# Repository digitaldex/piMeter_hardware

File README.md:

# piMeter - a SmartMeter for Raspberry Pi

Repo got cleaned up. You can find the new Software Version in my [piMeter_grafana](https://github.com/digitaldex/piMeter_grafana) Repo.

This one here is now only for the Hardware Part of this Project.

## Board

## Case

## Schematics
[piMeter Schematics](https://github.com/digitaldex/piMeter_hardware/blob/master/eagle/Schematics.pdf)

## Ressources

[ADE9000 Datasheet](http://www.analog.com/media/en/technical-documentation/data-sheets/ADE9000.pdf)

[bcm2835 Library](http://www.airspayce.com/mikem/bcm2835/)

[InfluxDB Library](https://github.com/orca-zhang/influxdb-cpp)

[www.digitaldex.de](http://www.digitaldex.de)

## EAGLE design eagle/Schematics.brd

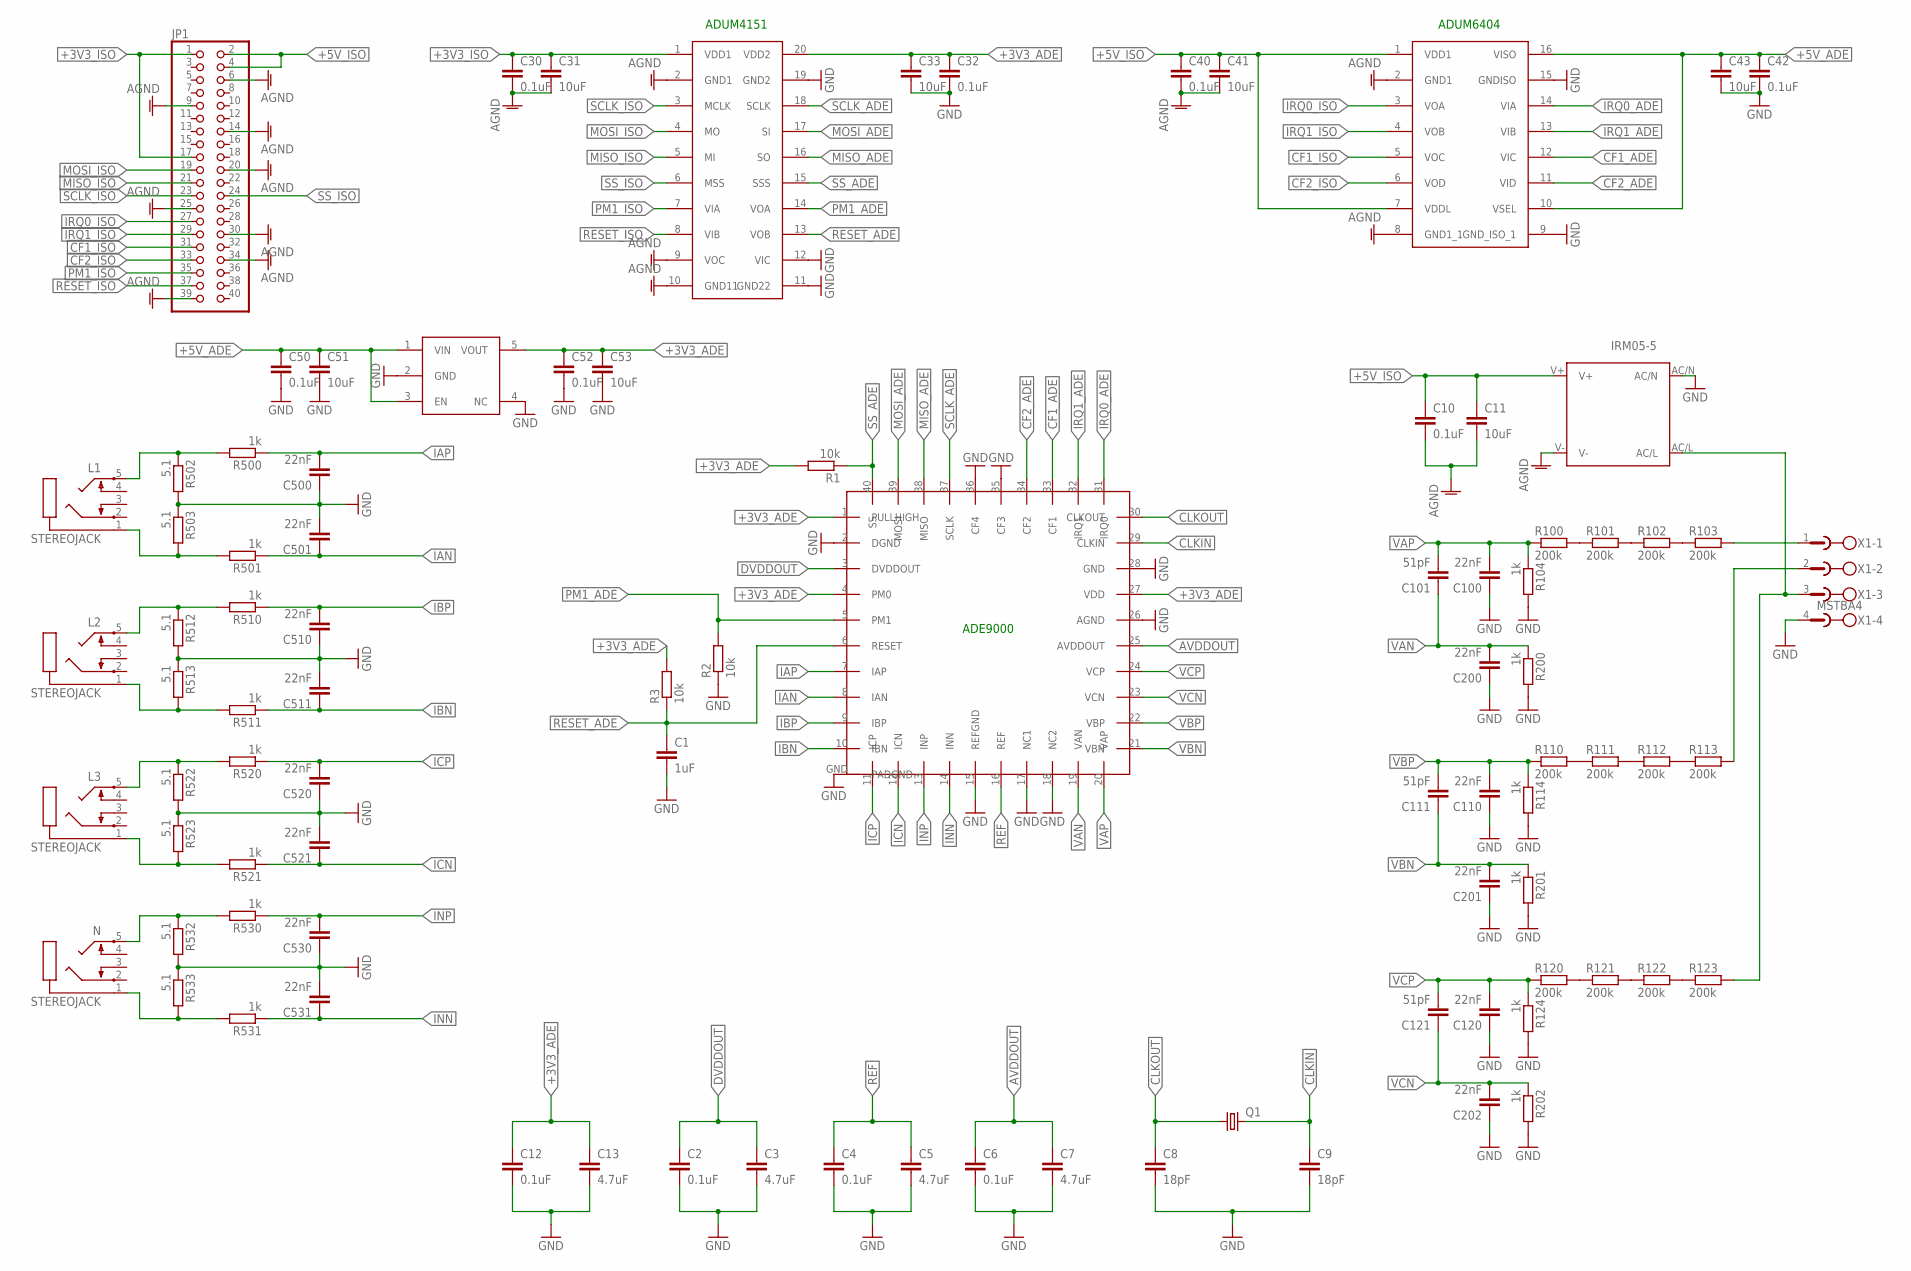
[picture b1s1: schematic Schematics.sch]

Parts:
ADE9000: ADE9000; LFCSP40
ADUM4151: ADUM4151; SOIC20R
ADUM6404: ADUM6404; SOIC16R
C1: 1uF; C0805
C2, C4, C6, C10, C12, C30, C32, C40, C42, C50, C52: 0.1uF; C0805
C3, C5, C7, C13: 4.7uF; C0805
C8, C9: 18pF; C0805
C11, C31, C33, C41, C43, C51, C53: 10uF; C0805
C100, C110, C120, C200, C201, C202, C500, C501, C510, C511, C520, C521, C530, C531: 22nF; C0805
C101, C111, C121: 51pF; C0805
IRM05-5: IRM_05/10
JP1: PINHD-2X20; 2X20
L1, L2, L3: STEREOJACK; STX3100
N: STEREOJACK; STX3100
Q1: CRYSTALCTS406; CTS406
R1, R2, R3: 10k; M0805
R100, R101, R102, R103, R110, R111, R112, R113, R120, R121, R122, R123: 200k; M1206
R104, R114, R124, R200, R201, R202, R500, R501, R510, R511, R520, R521, R530, R531: 1k; M0805
R502, R503, R512, R513, R522, R523, R532, R533: 5.1; M0805
U$5: ADP122AUJZ-3.3-R7; TSOT23-5L
X1: MSTBA4

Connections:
+3V3_ADE: ADE9000.1 (PULLHIGH), ADE9000.4 (PM0), ADE9000.27 (VDD), ADUM4151.20 (VDD2), C12.1, C13.1, C32.1, C33.1, C52.1, C53.1, R1.2, R3.2, U$5.5 (VOUT)
+3V3_ISO: ADUM4151.1 (VDD1), C30.1, C31.1, JP1.1, JP1.17
+5V_ADE: ADUM6404.10 (VSEL), ADUM6404.16 (VISO), C42.1, C43.1, C50.1, C51.1, U$5.1 (VIN), U$5.3 (EN)
+5V_ISO: ADUM6404.1 (VDD1), ADUM6404.7 (VDDL), C10.1, C11.1, C40.1, C41.1, IRM05-5.V+, JP1.2, JP1.4
AGND: ADUM4151.2 (GND1), ADUM4151.9 (VOC), ADUM4151.10 (GND11), ADUM6404.2 (GND1), ADUM6404.8 (GND1_1), C10.2, C11.2, C30.2, C31.2, C40.2, C41.2, IRM05-5.V-, JP1.6, JP1.9, JP1.14, JP1.20, JP1.25, JP1.30, JP1.34, JP1.39
AVDDOUT: ADE9000.25 (AVDDOUT), C6.1, C7.1
CF1_ADE: ADE9000.33 (CF1), ADUM6404.12 (VIC)
CF1_ISO: ADUM6404.5 (VOC), JP1.31
CF2_ADE: ADE9000.34 (CF2), ADUM6404.11 (VID)
CF2_ISO: ADUM6404.6 (VOD), JP1.33
CLKIN: ADE9000.29 (CLKIN), C9.1, Q1.3 (2)
CLKOUT: ADE9000.30 (CLKOUT), C8.1, Q1.1
DVDDOUT: ADE9000.3 (DVDDOUT), C2.1, C3.1
GND: ADE9000.2 (DGND), ADE9000.15 (REFGND), ADE9000.17 (NC1), ADE9000.18 (NC2), ADE9000.26 (AGND), ADE9000.28 (GND), ADE9000.35 (CF3), ADE9000.36 (CF4), ADE9000.GND, ADUM4151.11 (GND22), ADUM4151.12 (VIC), ADUM4151.19 (GND2), ADUM6404.9 (GND_ISO_1), ADUM6404.15 (GNDISO), C1.2, C2.2, C3.2, C4.2, C5.2, C6.2, C7.2, C8.2, C9.2, C12.2, C13.2, C32.2, C33.2, C42.2, C43.2, C50.2, C51.2, C52.2, C53.2, C100.1, C110.1, C120.1, C200.1, C201.1, C202.1, C500.1, C501.2, C510.1, C511.2, C520.1, C521.2, C530.1, C531.2, IRM05-5.AC/N, R2.1, R104.2, R114.2, R124.2, R200.2, R201.2, R202.2, R502.2, R503.1, R512.2, R513.1, R522.2, R523.1, R532.2, R533.1, U$5.2 (GND), U$5.4 (NC), X1.4
IAN: ADE9000.8 (IAN), C501.1, R501.1
IAP: ADE9000.7 (IAP), C500.2, R500.1
IBN: ADE9000.10 (IBN), C511.1, R511.1
IBP: ADE9000.9 (IBP), C510.2, R510.1
ICN: ADE9000.12 (ICN), C521.1, R521.1
ICP: ADE9000.11 (ICP), C520.2, R520.1
INN: ADE9000.14 (INN), C531.1, R531.1
INP: ADE9000.13 (INP), C530.2, R530.1
IRQ0_ADE: ADE9000.31 (IRQ0), ADUM6404.14 (VIA)
IRQ0_ISO: ADUM6404.3 (VOA), JP1.27
IRQ1_ADE: ADE9000.32 (IRQ1), ADUM6404.13 (VIB)
IRQ1_ISO: ADUM6404.4 (VOB), JP1.29
MISO_ADE: ADE9000.38 (MISO), ADUM4151.16 (SO)
MISO_ISO: ADUM4151.5 (MI), JP1.21
MOSI_ADE: ADE9000.39 (MOSI), ADUM4151.17 (SI)
MOSI_ISO: ADUM4151.4 (MO), JP1.19
unnamed: R121.2, R122.1
unnamed: R102.2, R103.1
unnamed: R103.2, X1.1
unnamed: L1.5, R500.2, R502.1
unnamed: L1.1, R501.2, R503.2
unnamed: L2.5, R510.2, R512.1
unnamed: L2.1, R511.2, R513.2
unnamed: L3.5, R520.2, R522.1
unnamed: L3.1, R521.2, R523.2
unnamed: N.5, R530.2, R532.1
unnamed: N.1, R531.2, R533.2
unnamed: R101.2, R102.1
unnamed: R111.2, R112.1
unnamed: R112.2, R113.1
unnamed: R122.2, R123.1
unnamed: R113.2, X1.2
unnamed: IRM05-5.AC/L, R123.2, X1.3
unnamed: R110.2, R111.1
unnamed: R100.2, R101.1
unnamed: R120.2, R121.1
PM1_ADE: ADE9000.5 (PM1), ADUM4151.14 (VOA), R2.2
PM1_ISO: ADUM4151.7 (VIA), JP1.35
REF: ADE9000.16 (REF), C4.1, C5.1
RESET_ADE: ADE9000.6 (RESET), ADUM4151.13 (VOB), C1.1, R3.1
RESET_ISO: ADUM4151.8 (VIB), JP1.37
SCLK_ADE: ADE9000.37 (SCLK), ADUM4151.18 (SCLK)
SCLK_ISO: ADUM4151.3 (MCLK), JP1.23
SS_ADE: ADE9000.40 (SS), ADUM4151.15 (SSS), R1.1
SS_ISO: ADUM4151.6 (MSS), JP1.24
VAN: ADE9000.19 (VAN), C101.1, C200.2, R200.1
VAP: ADE9000.20 (VAP), C100.2, C101.2, R100.1, R104.1
VBN: ADE9000.21 (VBN), C111.1, C201.2, R201.1
VBP: ADE9000.22 (VBP), C110.2, C111.2, R110.1, R114.1
VCN: ADE9000.23 (VCN), C121.1, C202.2, R202.1
VCP: ADE9000.24 (VCP), C120.2, C121.2, R120.1, R124.1

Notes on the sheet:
ADUM4151
ADE9000
ADUM6404

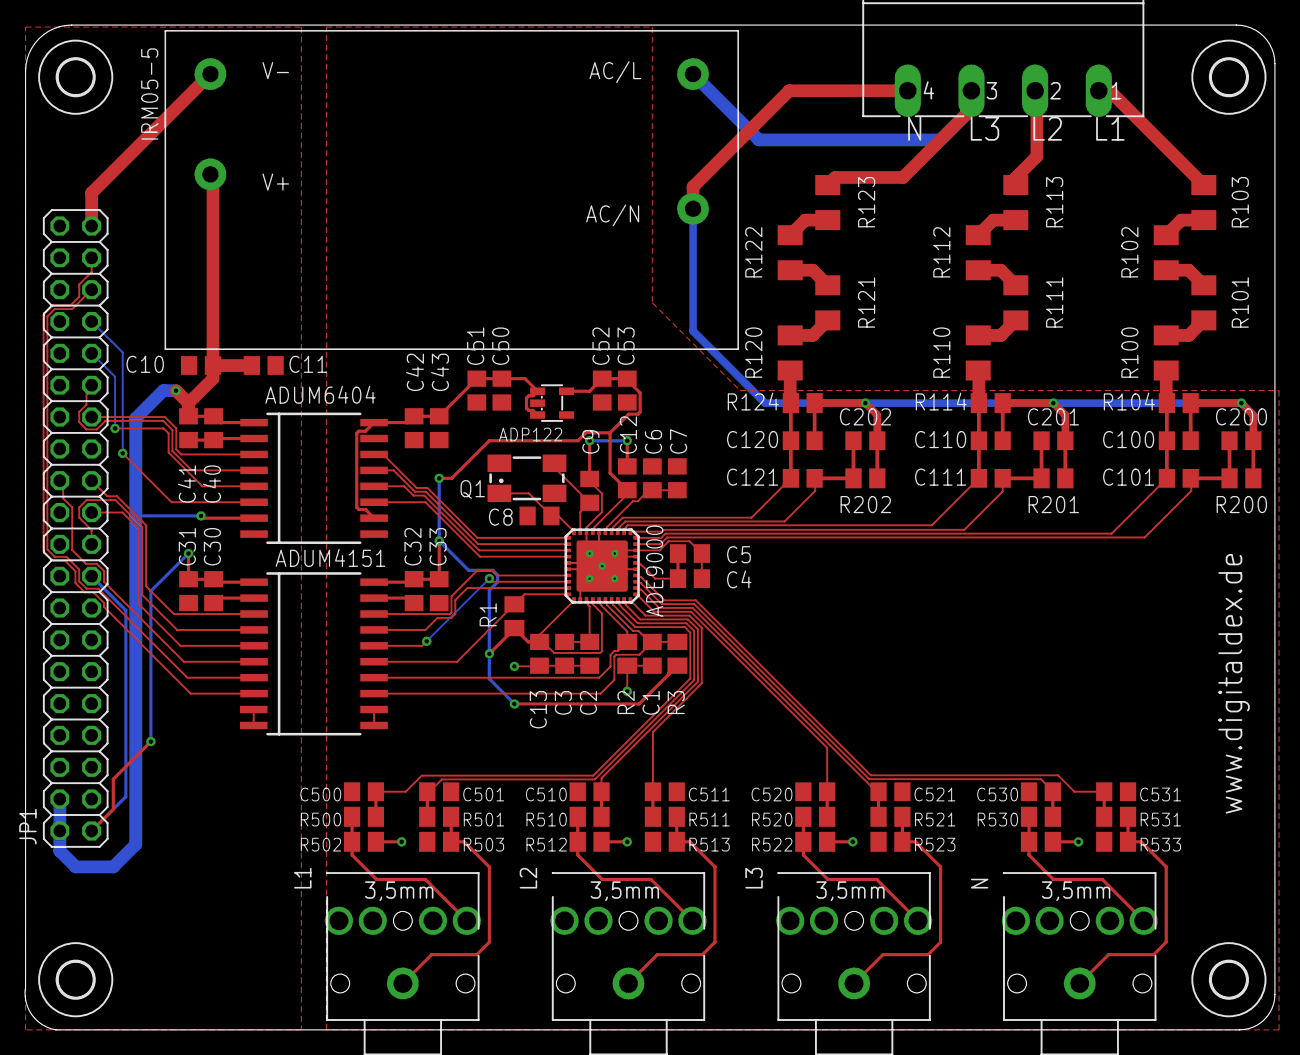
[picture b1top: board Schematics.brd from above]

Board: 2 copper layers, 99.7 x 80.2 mm, 95 parts (0 on the bottom side), 65 nets.

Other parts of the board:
U$1, U$2, U$3, U$4: 2,8

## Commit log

2017-12-30 Init
2018-01-03 Create LICENSE
2018-01-16 Added Websockets
2018-01-21 fixed symbol; routed GND; rerouted some signals with more space
